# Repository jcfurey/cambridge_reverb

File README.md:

# Vox Cambridge Reverb (V1031/V1032) — Electronics Rebuild

Complete electronics rebuild of a Vox Cambridge Reverb solid-state guitar amplifier:
the original electronics are gutted and replaced with modern parts while preserving
the original functionality, the front/rear panel layout (no new holes), and the
chassis. Guitar-frequency and 10″ alnico-speaker optimized throughout.

> **Honesty up front:** the Part 1–10 design docs were **reconstructed** from a prior
> conversation (see `docs/PROVENANCE.md`); some values were gap-filled, and a few stages
> are designed substitutes. The KiCad project, BOM, order package and ngspice sims are
> **generated and tool-verified** — both boards are fully routed with 0 DRC errors, and
> `kicad/gen/verify.py` checks them pin for pin against the schematic and the
> datasheets. **Nothing has been built or measured.** A datasheet audit and new simulations
> found six faults in November 2026 that ERC and DRC could not see (errata #25–#30), and
> measuring the copper found a slotted ground plane and blind vias (errata #31);
> expect the bench to find more. Order one batch, bring it up on a series lamp.

## Core design decisions

| Block | Replacement |
|-------|-------------|
| Power amp | LM1875T (replaces germanium push-pull; eliminates driver transformer T2) |
| Preamp JFETs | MMBF5457 (SOT-23: direct on the SMD variant, on an adapter for THT) or J113 (2N5457 discontinued) — **availability watch**; pins 1 D / 2 S / 3 G (errata #18) |
| Reverb / tremolo | TL072 ×2 (no transformer T3): IC1 = tank driver + **active wet/dry summer**; IC2 = tremolo LFO + **output buffer** |
| Reverb pan | Accutronics 4FB2A1C (~1475 Ω input) — 8 Ω 4AB3C1B is **incompatible** |
| Tremolo modulation | Xvive VTL5C1 or DIY LED/LDR optocoupler (axial part, **pad 1 = LED cathode** — errata #25), driven by a TL072 Wien LFO — **symmetric, dual-gang 250 k speed pot, 0.6–10.6 Hz** (errata #19: the recovered single-arm pot could not oscillate at tremolo rates); LED-limited LFO + **2N3904 emitter-follower LED driver, 14 dB depth** (errata #22: as drawn the vactrol LED ran at 7 mA DC — a fixed −20 dB pad with 1.7 dB of wobble) |
| Footswitch | Three contacts to ground on the original DIN connector: reverb off, tremolo off, **MRB on** — the MRB tank returns to ground *through* the pedal, so with no pedal the amp is flat (errata #27: the lines used to end on pull-downs and the 577 Hz band-pass was permanently in circuit) |
| Preamp gain | Two JFET stages, source-bypass caps `C_s1` / `C_s2` **optional and off by default**: 21 dB, clean to ~0.3 V pk; fitted they give 33 / 45 dB and an overdriven second stage (errata #28) |
| Power | Centre-tapped secondary into the KBP410G as a **two-diode full-wave** (link `JP_BR` open; fit it only for a single 24 V winding — errata #26: CT and the bridge's "−" were both grounded, a short across each half-winding); LM317T-regulated +17 V rail with **`C_adj`** and an RC-decoupled **`+17V_PRE`** rail for the JFET stages (errata #21: the regulator's noise sat 23 dB above the JFET floor); split `VBIAS_R`/`VBIAS_T`/`VBIAS_3` mid-rails; `VREG_IN` RC pre-filter; **bypassed LM1875 bias divider** (errata #21: as drawn it fed rail ripple ×23 to the speaker — 0.4 Vrms of hum) |
| Tone | **Bass + Treble** (the panel's pots) on a passive James / Thomas-Vox network with a TL074 buffer + make-up (IC3), 470 pF chime cap as a bright cap, and a **MID CUT toggle** (−9.6 dB @ ~800 Hz, broad) in the line-reverse switch hole — errata #20 (the recovered 470 pF-only coupling passed no bass at all) |

## What's verified (all via real tools — `kicad/gen/build.sh smd`, `kicad/gen/verify.py smd`)
- **One gate:** `kicad/gen/verify.py` — **90 of 90 checks** on the SMD board, 79 of 79 on the THT board (`kicad/reports/verify-*.txt`). It reads the finished files, not the generator's data: ERC, DRC, schematic-to-board parity pin for pin, a pin-function audit against the datasheets, net-level electrical assertions (clamp-diode direction, rectifier topology, electrolytic polarity at the DC operating point, supply pins, pot directions, footswitch), silkscreen, JLCPCB's published limits, the star-ground topology and a solve of the return currents in the routed copper, ground loops (on the board, through the hardware, through the wiring), geometric and DC offsets, the ground-system ("RF") rules measured on the finished copper, order-package consistency, and the SPICE suite with a schematic-to-netlist value cross-check.
- **Schematic:** generated by `kicad/gen/gen_kicad.py` → 8 hierarchical sheets, **ERC 0 violations** (KiCad 8.0.9). SMD build: 162 components + 29 test points, 89 nets; the THT build has 182 parts (that board is full: a few parts are single where the SMD board uses JLCPCB-basic multiples, and three bleeders live off the board).
- **The JLCPCB board** (`kicad/smd/`, **170 × 105 mm**, 4 layers): **256 of 256 connections routed, 0 DRC errors, 0 warnings** with JLCPCB's limits as constraints. 105 small parts (0805 / 1206 / SMA / SOT-23) are placed by JLCPCB; 36 through-hole parts — power devices, electrolytics, socketed op-amps, the bench-trimmed resistors, the bright cap — are soldered by hand. Every part is labelled on the silkscreen and every wiring pad says what it is for.
- **Star ground** (errata #32, `kicad/gen/ground_audit.py` → `kicad/reports/ground-*.md`): the planes are signal ground only; transformer centre tap, reservoir, speaker return and the LM1875's ground pin are separate routed nets that meet the planes through one 0 Ω link at the speaker's return terminal. Solving the routed copper as a resistor network puts the ground-return buzz at the speaker at **13 µV** at idle (the single-net board: 4.4 mV, 31 dBA at 1 m) and no speaker current in the planes.
- **Ground loops and offsets** (errata #37–#43, `kicad/gen/loop_audit.py`, `offset_audit.py`, `tidy_tracks.py` → `kicad/reports/loops-*.md`, `offsets-*.md`): no closed loop in any routed net; no ground copper under the mounting hardware; the wiring mistakes that would bridge the star are simulated and listed as eight rules in Part 3; the reverb tank's shield loop — the largest in the amplifier — is opened by a 10 Ω return on the SMD board (7 µV (7 hot) at the speaker for a reference stray field, against 903 µV (902 hot)). Every track end lands on the centre of its pad or via. Three DC faults found by simulating the real bias levels with no signal: the output buffer followed the tremolo oscillator's bias rail (0.37 V pp of LFO at the speaker, now 8 mV), the footswitch thumped (2.5 V pp, now 5 mV), and the vactrol's blocking capacitor charged its node while the tremolo was off (8–19 V pp on re-engaging, now 0.04 V).
- **Power-amp stability** (errata #35, `spice/ac_pa_stability.cir`): the roll-off capacitor across the LM1875's feedback resistor is gone — it took the noise gain of a gain-≥-10 amplifier to 1 (−9° / −1° of phase margin in a three-pole model); the 7.7 kHz roll-off is an RC at the input, +68° / +76°.
- **Ground system** (errata #31, `kicad/gen/rf_audit.py` → `kicad/reports/rf-*.md`): signal / **solid ground** / signal / **solid ground**, nothing routed on a plane, each signal layer 0.21 mm from its own plane; plane openings sized by the holes so no slot forms along a row of pins (3 openings over 5 mm in the inner plane, was 31); copper 0.5 mm back from the edge with a ground via fence every 5 mm; a via beside every SMD ground pad and 340 ground vias in all, no point further than 15 mm from one; top pour 0.5 mm from every trace and 1.0 mm from high-impedance nets. Stray capacitance of every sensitive net is tabulated: the lowest corner is `TONE_OUT`, 25 pF → 101 kHz. All vias are plain through vias.
- **Order package** (`production/smd/`, built by `kicad/gen/fab_jlcpcb.py`): Gerber + drill zip, assembly BOM with **an LCSC part number on every one of its 28 lines** (each looked up in JLCPCB's library — stock, class, package; `kicad/gen/jlc_parts.py --check` re-reads them), pick-and-place file in JLCPCB's format with the SOT-23 rotation offset, assembly drawing. 21 basic / 4 preferred / **3 extended** part types: assembly fees ≈ $21 for five boards, ≈ $45 with the parts (`kicad/gen/jlc_cost.py`).
- **THT board** (`kicad/`, 190 × 115 mm, the original outline): same circuit, same stack, same star ground, all through-hole, **245 of 245 routed, 0 DRC errors, 0 warnings**; ground-return hum 27 µV. It is full — no room for the tank loop breaker or the three convenience bleeders, which Part 3 covers with wiring rules.
- **Routing:** `kicad/gen/route_board.py` autoroutes headlessly with Freerouting on the two signal layers; `kicad/gen/finish_routes.py`, a small maze router that applies the project's rules as written, closes the 7–13 links Freerouting leaves (signal-level branches of power nets, the tank drive), re-ordering and starting over if one finds no path; `kicad/gen/stitch.py` then stitches the grounds. Keepout areas between every part's pins, nets classed by impedance, RC stoppers at the two antenna inputs (errata #24). See `kicad/PCB-NOTES.md`.
- **BOM:** generated from the schematic by `kicad/gen/gen_bom.py` (1:1 with the netlist, no drift) → `bom/bom.csv` + `bom/bom-grouped.csv` (THT) and `bom/bom-smd*.csv` (variant).
- **Noise / hum / crosstalk / thermal** (`docs/06c-…`): `.noise` of the whole front end with the regulator's own noise (EIN 37 → 2.7 µV, SNR at 12 W 34 → 57 dB after errata #21), rail-ripple paths (hum 408 mV → 0.3 mV at the speaker), a vactrol-level tremolo model, a geometric **crosstalk audit** of both routed boards, and an electro-thermal LM1875 model (2.5 K/W sink: Tj 97 °C at 40 °C ambient, worst-case sine).
- **SPICE:** `spice/run_all.sh` runs 16 ngspice block checks (preamp bias, reverb driver, MRB engaged / bypassed, tremolo LFO and its **DC thumps and LFO feed-through with no signal**, power amp and its **loop stability**, **rail-aware** reverb summer and its **stability against stray capacitance**, **rail-aware** tone stack, Class-A stage, front-end noise, hum paths, tremolo depth with the footswitch, LM1875 thermal, **preamp headroom at pickup levels**) **plus 6 parameter sweeps** and saves every result table to **`spice/results/`** (committed evidence).

## Honest engineering notes (from the audit/roast passes — see `docs/roast-2026-06-16.md`)
- 🔴 **Output power ≈ 12 W, not 18 W.** A single 33.5 V rail can't swing the 17 V peak that 18 W into 8 Ω needs; the LM1875 ceilings at ~12 W clean (~1.8 dB down). Fine for a 10″ combo.
- 🔴 **Fit a MAINS (primary) fuse** — the design's other fuse is only on the secondary. Required for safety.
- 🔴 **Know your transformer before you wire it** (errata #26): centre tap to `CT` with `JP_BR` open, *or* a single winding with `JP_BR` fitted and `CT` empty.
- ⚠️ **Chassis fit:** the THT board is **190×115 mm** (the original 25-5274-2 outline), the JLCPCB board **170×105 mm**. Nobody has measured the actual chassis (errata #9); set `BW, BH` in `gen_pcb.py` and run `build.sh` if it disagrees — the placer and both routers adapt.

## Key constraints
- No new holes in original panels; all improvements internal only.
- MRB tuned to 600 Hz (original spec), switched by the footswitch; tremolo rate LED is PCB-mounted (diagnostic).
- Original 6-pin DIN footswitch connector and pedal retained (one contact to ground per effect).

## Repository layout

```
docs/         Parts 1–10, errata, PROVENANCE, audits (component-availability, roast)
kicad/        Generated KiCad project + gen/ scripts (build.sh, verify.py, …); symbols/
              footprints/ reports/; SCHEMATIC-BUILD / PCB-NOTES / PCB-AUDIT
spice/        ngspice block sims + run_all.sh + models/ (LTspice power-amp kept for provenance)
bom/          bom.csv (generated), bom-grouped.csv, cross-check
datasheets/   sourcing pointers (SOURCES.md)   photos/  capture checklist
production/   JLCPCB order package (smd/: Gerber zip, BOM with LCSC numbers, CPL) + checklist
```

## Tools
- **EDA / verification:** KiCad 8.0.9 (`kicad-cli`, `pcbnew` Python). `kicad/gen/build.sh smd|tht` rebuilds a board end to end (generate → Freerouting 1.9.0 → `finish_routes.py` → reports → order package → verify; needs Java, the Freerouting jar, xvfb, numpy, scipy, ngspice); `kicad/gen/verify.py smd|tht` checks an existing build
- **Datasheets:** `datasheets/` holds the manufacturer PDFs the footprints and pinouts were taken from, with a manifest (`SOURCES.md`: file, revision, checksum, which decision it backs)
- **Simulation:** ngspice (`spice/run_all.sh`); LTspice netlist kept for the power amp
- **PCB fab / sourcing:** JLCPCB · Mouser / Digikey

## Status
Reconstructed Parts 1–10 + errata, then verify / audit / roast passes and, in November
2026, a pinout and wiring audit that found what the rule checks could not (reversed
clamp diodes and vactrol LED, a shorted centre-tapped rectifier, a footswitch that
switched nothing, a preamp with no clean range — errata #25–#30), then a rebuild of the
copper to RF grounding practice (errata #31). Both boards are fully routed and
rule-clean, and the JLCPCB order package for the SMD / THT board is in `production/smd/`.
**Remaining, none of it doable from a keyboard:** measure the chassis, identify the
transformer, build one board and bring it up on a series lamp, trim the three JFET
source resistors, and tune tremolo depth and the MRB by ear. See `production/CHECKLIST.md`
and `CHANGELOG.md`.

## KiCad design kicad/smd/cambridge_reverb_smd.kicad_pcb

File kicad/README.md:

# kicad/

KiCad project files.

## Present now
- `cambridge_reverb.kicad_pro` — project with reconciled design rules and **three
  net classes** from the consistency pass: Default 0.5 mm / Power 1.5 mm /
  HighCurrent 2.5 mm (errata #11–13). `+33V5`/`SPK_P`/`SPK_N`/`PA_OUT` are pre-assigned
  to HighCurrent by net-name pattern.
- `symbols/cambridge_reverb.kicad_sym` — custom symbols: `VTL5C1`,
  `Reverb_Tank_4FB2A1C`, `Footswitch_DIN6`.
- `footprints/cambridge_reverb.pretty/` — `VTL5C1` (axial, from the PerkinElmer drawing: pad 1 = LED cathode, errata #25), `Inductor_MRB_1H_Toroid`
  (2-pad, 25 mm), **`TO-220-5_Vertical_P1.70mm_LM1875`** (TI NDH inline TO-220-5
  with 1.45 mm pads — fixes the annular-ring DRC error of the stock footprint,
  PCB-AUDIT §1), **`Bridge_KBP_P3.81mm`** (Diodes KBP410G, DS39310, pins
  + ~ ~ −), **`TestPoint_THT_D2.0mm_Label`** (bench test point, value printed on
  silk) and the **`WirePad_*`** wiring pads. `Wiring_Edge_Array_35` (35-pad edge connector) is also in the
  library but **currently unused** — `gen_pcb.py` places per-connector
  **`WirePad_1x0N_P2.54mm_D1.2mm` / `WirePad_1x0N_P5.08mm_D1.5mm`** pads (the Part 4
  signal / power wire-pad sizes) along the wiring edge instead; the 35-pad array
  is kept as a reference (roast R4).
- `sym-lib-table` / `fp-lib-table` — register the project libraries (`${KIPRJMOD}`).
- `netlist-notes.txt` — recovered per-sheet connections (power amp, reverb,
  tremolo, MRB).
- `SCHEMATIC-BUILD.md` — step-by-step to build the 8 hierarchical sheets.

## Generated schematic (now present)
- `cambridge_reverb.kicad_sch` (root) + 8 hierarchical sheets — `power_supply`,
  `preamp`, `tone_stack`, `reverb`, `tremolo`, `mrb`, `power_amp`, `switching`.
  They open in KiCad 7/8, **pass ERC with 0 violations** (KiCad 8.0.9), and
  netlist cleanly (154 components + 28 test points, 87 nets, 0 unconnected pins; the
  SMD build in `smd/` has 162 + 29 and 89 nets — errata #36, #38–#41).
- `symbols/cr_primitives.kicad_sym` — self-contained primitive symbols used by
  the generated sheets.
- `gen/gen_kicad.py` — the generator (regenerate: `python3 kicad/gen/gen_kicad.py`).
- `SCHEMATIC-BUILD.md` — how the sheets are wired, what's verified, and the
  known simplifications to finish before a build.

## PCB (generated: zoned placement + headless autoroute)
- `cambridge_reverb.kicad_pcb` — generated by `gen/gen_pcb.py`: 178 footprints
  placed into the **Part 5 floor-plan zones** (Input/Preamp | Tone | Reverb/Trem |
  Power Amp | PSU, left→right), off-board connectors on the bottom wiring edge,
  LM1875/LM317 on the top edge with the 10 mm keep-out, 4× M3 mounting holes,
  190×115 mm outline, **4 copper layers** (F.Cu signal + ground pour, In1 ground plane,
  In2 signal, B.Cu ground plane — nothing routed on a plane; ground via fence every
  5 mm), keepout areas between every part's pins, JLCPCB
  design rules + `cambridge_reverb.kicad_dru` impedance-class rules, every part labelled
  on the silkscreen. **Fully routed: 234 / 234 connections, 0 DRC errors, 0 warnings.**
- `gen/route_board.py` — **headless autoroute** via Freerouting (DSN → SES →
  import, GND pour refilled). Needs Java + the Freerouting jar (git-ignored; see
  the script docstring). It also injects the per-class *routing* clearances
  (HighCurrent 0.6 mm, TankDrive 1.2 mm) that `cambridge_reverb.kicad_dru` checks
  afterwards for tracks/vias. Routing status and numbers: `PCB-NOTES.md`.
- `gen/finish_routes.py` — a grid **maze router for the links Freerouting leaves open**
  (signal-level branches of power nets, the tank drive), applying the `.kicad_dru` rules
  as written; KiCad's DRC judges the result.
- `gen/build.sh smd|tht` — the whole chain in one command; `gen/verify.py smd|tht` —
  the gate (parity, pin-function audit, electrical assertions, order package, SPICE).
- `gen/fab_jlcpcb.py`, `gen/jlc_parts.py` — the **JLCPCB order package** in
  `production/smd/` and the looked-up LCSC part for every assembly line.
- `gen/stitch.py` — **ground vias**: a via beside every SMD ground pad before routing,
  a 7.5 mm stitching grid after it, unused inner-layer pad copper removed (errata #31).
  Also the via escapes for small parts on high-current nets (`fanout_taps`) and the
  charging pulses' own power-ground run (`split_ct` / `join_ct`, errata #43).
- `gen/tidy_tracks.py` — **geometric clean-up after routing**: every track end onto the
  centre of its pad or via, unused via escapes out, closed copper rings opened, plane
  necks under 0.2 mm closed; KiCad's DRC vetoes each change (errata #42).
- `gen/loop_audit.py` — **ground-loop audit** (`reports/loops-*.md`): closed loops in
  the routed copper, the area of the big current loops, copper under the mounting
  hardware, the power-ground star, wiring mistakes simulated, and the loops that close
  off the board priced for a reference stray field (errata #40, #41, #43).
- `gen/offset_audit.py` — **offsets audit** (`reports/offsets-*.md`): track ends,
  placement centroids and rotations, nets with no DC path, supply-trace voltage drops
  (errata #39, #42).
- `gen/ground_audit.py` — the **ground-return solver** behind both (`reports/ground-*.md`,
  errata #32).
- `gen/rf_audit.py` — **ground and parasitics audit** of the finished copper: plane
  openings, edge pull-back, pour gaps, fence and stitching density, and the stray
  capacitance of every sensitive net with the corner it makes (`reports/rf-*.md`).
- `gen/crosstalk_audit.py` — geometric **crosstalk screen** of a routed board:
  mutual capacitance of parallel runs between power/AC/tank-drive nets and the
  sensitive nodes, coupled level vs signal, loop gain (Part 6c §4).
- `gen/jlc_cost.py` — JLCPCB assembly **cost model** from the generated BOM (joints,
  basic vs extended part types) — Part 4.
- `gen/check.sh tht|smd [--no-regen]` — regenerate + ERC/DRC with the **JLCPCB
  fab limits** stored in both `.kicad_pro` files (hole-to-hole 0.5, hole-to-copper
  0.3, annular 0.18, mask dam 0.1 mm …) and the custom `.kicad_dru` rules.

## `smd/` — the mixed SMD/THT variant (same schematic, second footprint profile)
- `smd/cambridge_reverb_smd.kicad_pro/.kicad_sch` + the 8 sheets, `smd/cambridge_reverb_smd.kicad_pcb`
  (**170 × 105 mm**; fully routed, 0 DRC errors — the board `production/smd/` is built from): generated with `--profile smd` by the
  same scripts. Small passives and semis are SMD (0805 R, 1206 C,
  SMA D, SOT-23 JFETs / BJT); power parts, all electrolytics, the socketed
  TL072s / TL074, the bench-trimmed JFET source resistors, connectors and test points stay
  THT. Lib tables point at the shared `../symbols` / `../footprints`.
  Details and routing status: `PCB-NOTES.md` (SMD variant section).

## Still to do
- Confirm the board size against the measured chassis (errata #9), then order per
  `production/smd/README.md` and `production/CHECKLIST.md`.
- The copper is machine-routed and rule-clean, not hand-tuned: look it over in the GUI if
  you care how it looks. `gerbers/` is a scratch folder for manual exports; the order
  package lives in `production/smd/`.

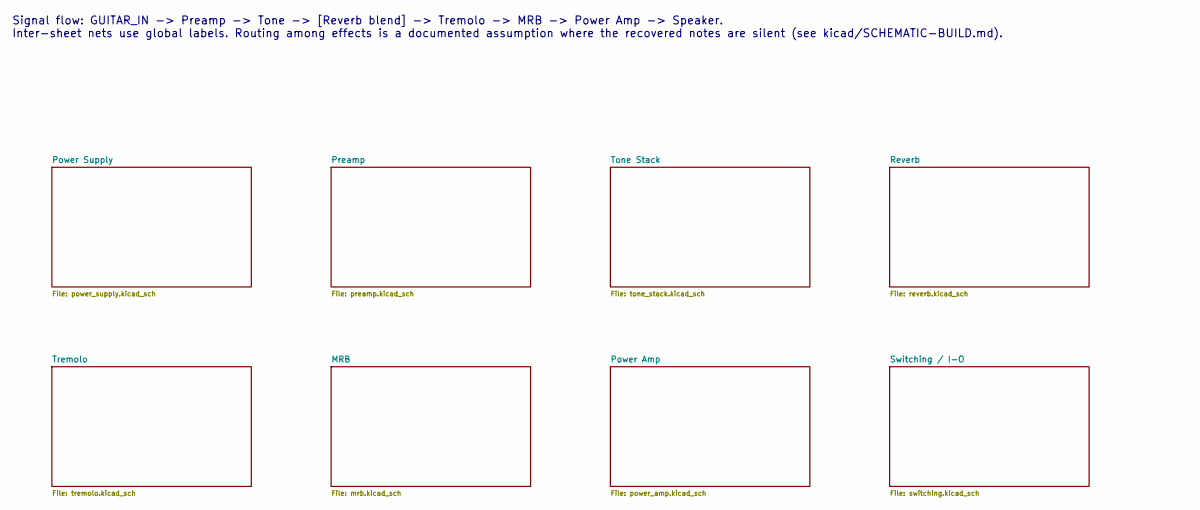
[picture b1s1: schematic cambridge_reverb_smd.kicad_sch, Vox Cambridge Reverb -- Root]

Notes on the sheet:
Signal flow: GUITAR_IN -> Preamp -> Tone -> [Reverb blend] -> Tremolo -> MRB -> Power Amp -> Speaker. Inter-sheet nets use global labels. Routing among effects is a documented assumption where the recovered notes are silent (see kicad/SCHEMATIC-BUILD.md).

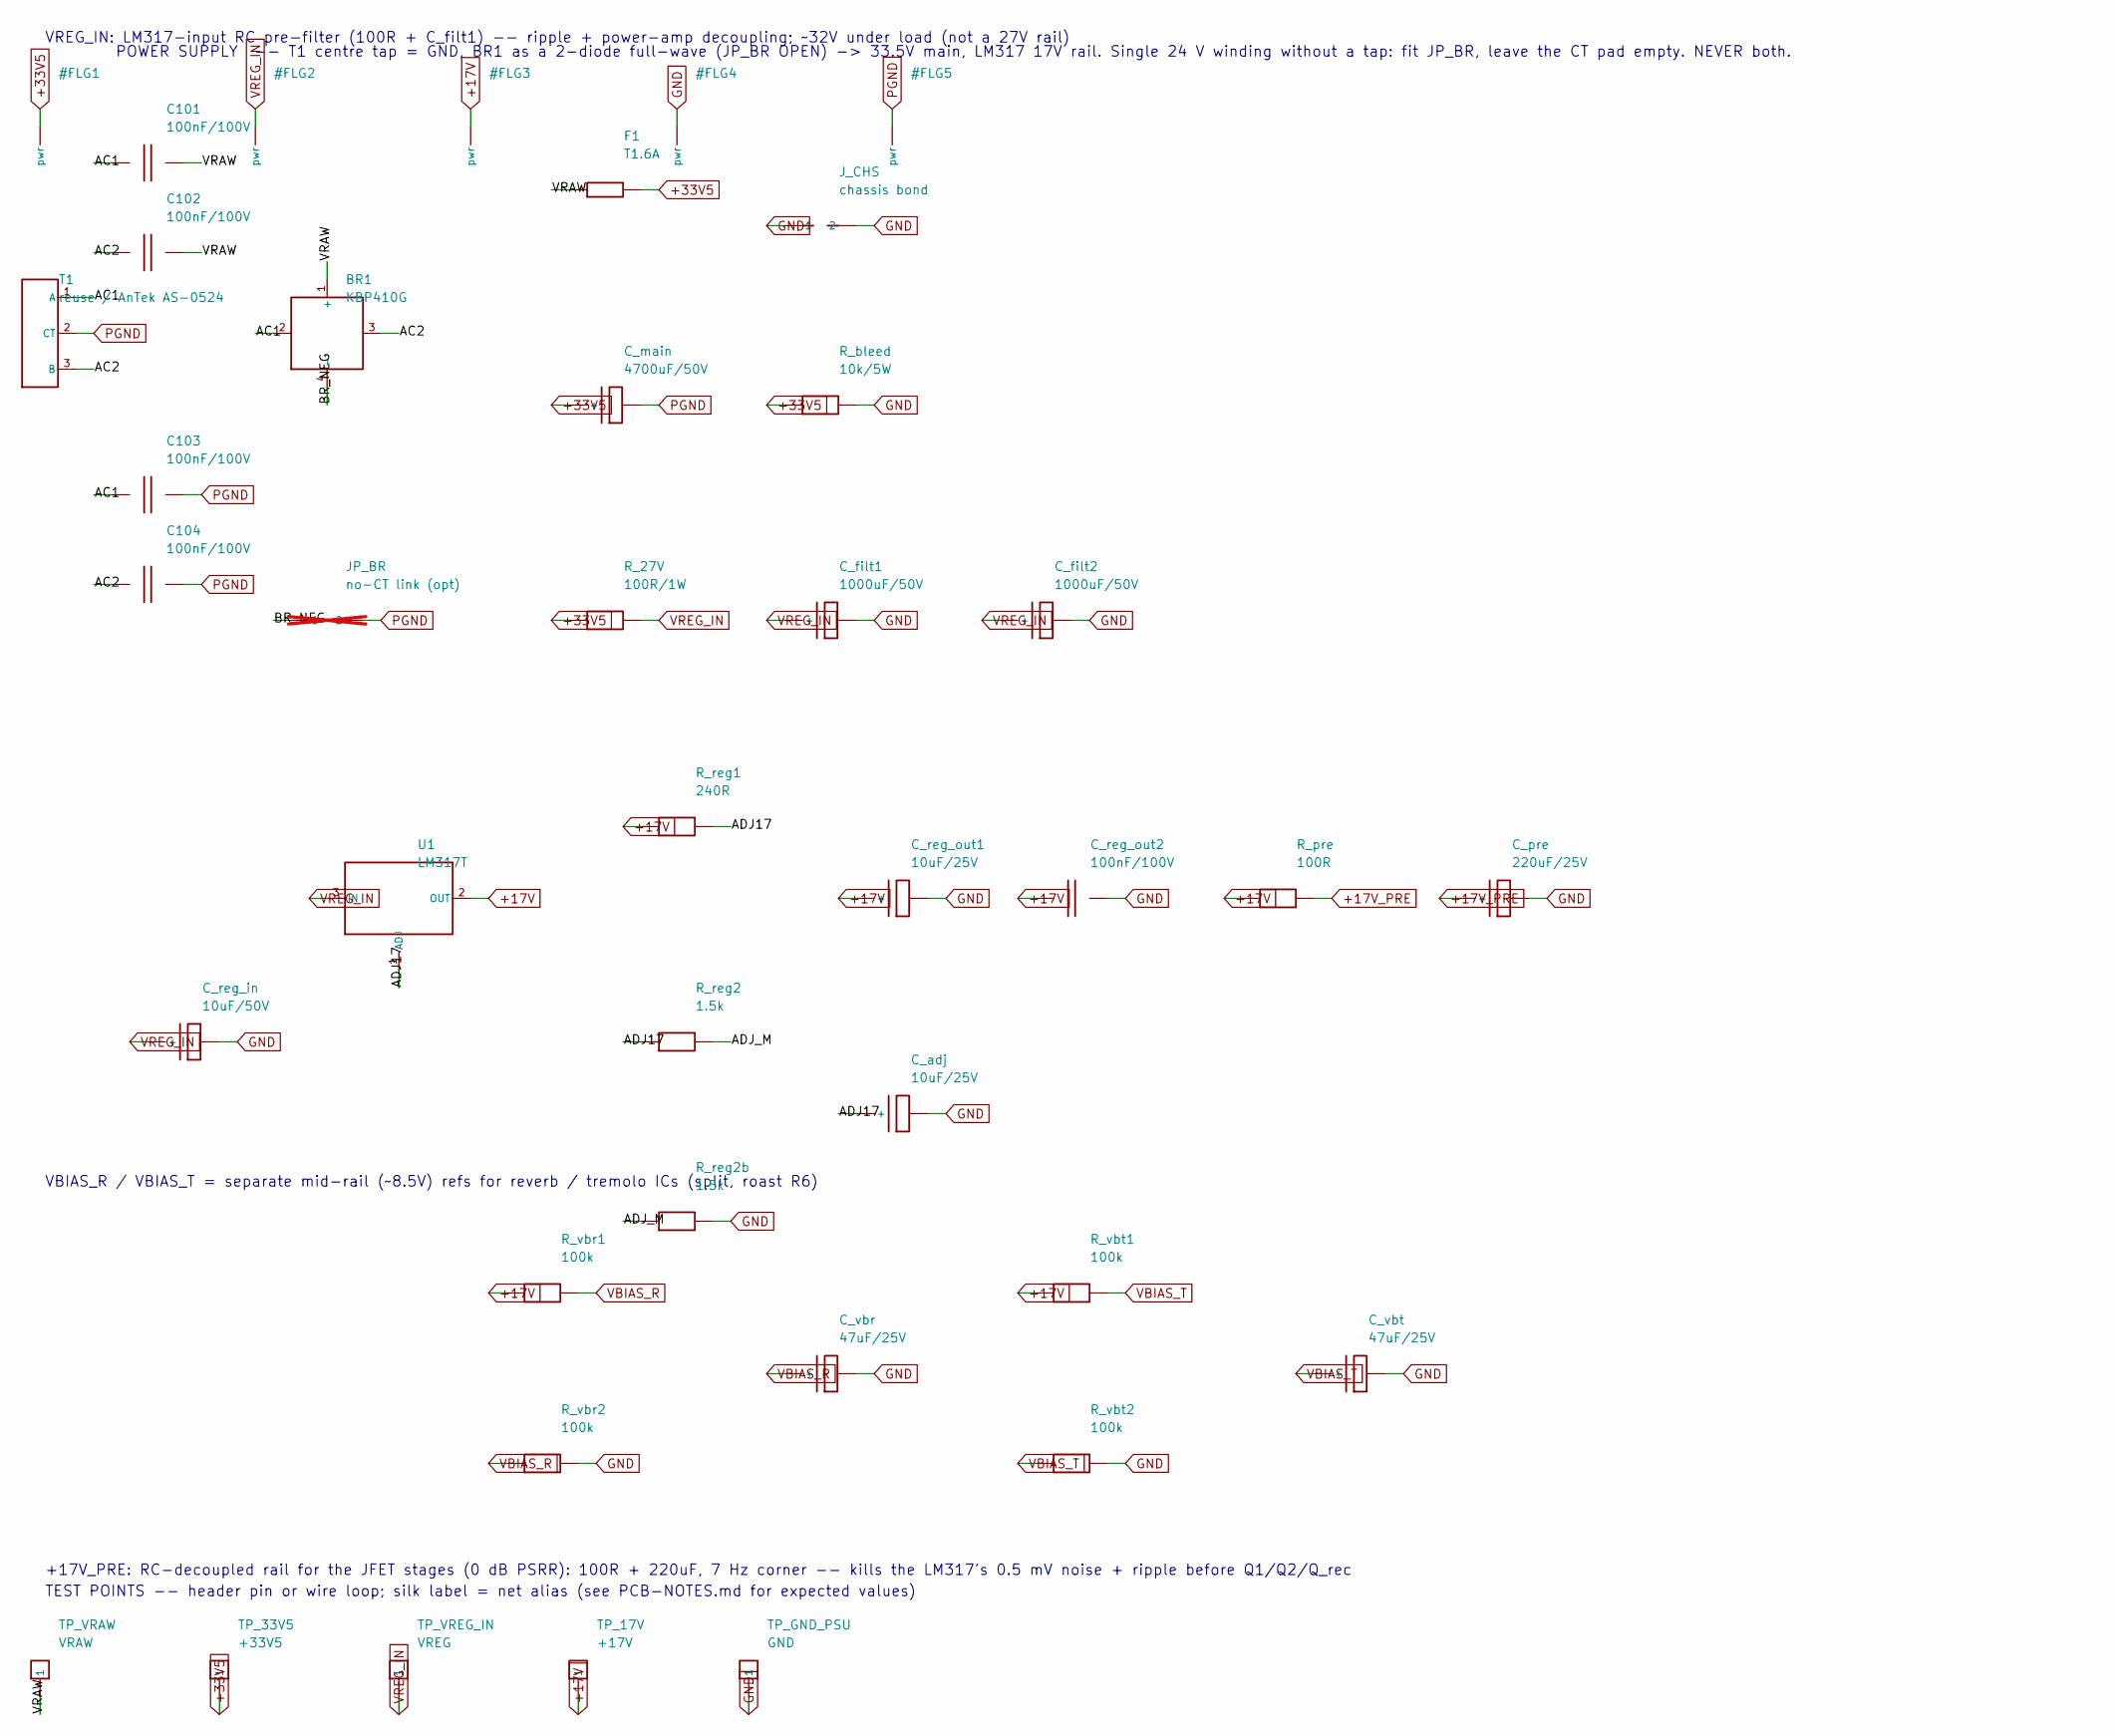
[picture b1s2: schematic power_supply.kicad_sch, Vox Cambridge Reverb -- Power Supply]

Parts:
BR1: KBP410G; Bridge_KBP_P3.81mm
C101, C102, C103, C104: 100nF/100V; C_0805_2012Metric
C_adj: 10uF/25V; CP_Radial_D5.0mm_P2.00mm
C_filt1, C_filt2: 1000uF/50V; CP_Radial_D12.5mm_P5.00mm
C_main: 4700uF/50V; CP_Radial_D18.0mm_P7.50mm
C_pre: 220uF/25V; CP_Radial_D6.3mm_P2.50mm
C_reg_in: 10uF/50V; CP_Radial_D5.0mm_P2.50mm
C_reg_out1: 10uF/25V; CP_Radial_D5.0mm_P2.50mm
C_reg_out2: 100nF/100V; C_0805_2012Metric
C_vbr: 47uF/25V; CP_Radial_D6.3mm_P2.50mm
C_vbt: 47uF/25V; CP_Radial_D6.3mm_P2.50mm
F1: T1.6A; Fuseholder_Clip-5x20mm_Eaton_1A5601-01_Inline_P20.80x6.76mm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
JP_BR: no-CT link (opt); WirePad_1x02_P5.08mm_D1.5mm; not fitted
J_CHS: chassis bond; WirePad_1x02_P5.08mm_D1.5mm
R_27V: 100R/1W; R_Axial_DIN0414_L11.9mm_D4.5mm_P15.24mm_Horizontal
R_bleed: 10k/5W; R_Axial_Power_L20.0mm_W6.4mm_P25.40mm
R_pre: 100R; R_0805_2012Metric
R_reg1: 240R; R_0805_2012Metric
R_reg2, R_reg2b: 1.5k; R_0805_2012Metric
R_vbr1, R_vbr2: 100k; R_0805_2012Metric
R_vbt1, R_vbt2: 100k; R_0805_2012Metric
T1: reuse / AnTek AS-0524; WirePad_1x03_P5.08mm_D1.5mm
TP_17V: +17V; TestPoint_THT_D2.0mm_Label
TP_33V5: +33V5; TestPoint_THT_D2.0mm_Label
TP_GND_PSU: GND; TestPoint_THT_D2.0mm_Label
TP_VRAW: VRAW; TestPoint_THT_D2.0mm_Label
TP_VREG_IN: VREG; TestPoint_THT_D2.0mm_Label
U1: LM317T; TO-220-3_Vertical

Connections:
+17V: C_reg_out1.1 (+), C_reg_out2.1, R_pre.1, R_reg1.1, R_vbr1.1, R_vbt1.1, TP_17V.1, U1.2 (OUT); also elsewhere on the board
+17V_PRE: C_pre.1 (+), R_pre.2; also elsewhere on the board
+33V5: C_main.1 (+), F1.2, R_27V.1, R_bleed.1, TP_33V5.1; also elsewhere on the board
AC1: BR1.2, C101.1, C103.1, T1.1 (A)
AC2: BR1.3, C102.1, C104.1, T1.3 (B)
ADJ17: C_adj.1 (+), R_reg1.2, R_reg2.1, U1.1 (ADJ)
ADJ_M: R_reg2.2, R_reg2b.1
BR_NEG: BR1.4 (-), JP_BR.1
GND: C_adj.2, C_filt1.2, C_filt2.2, C_pre.2, C_reg_in.2, C_reg_out1.2, C_reg_out2.2, C_vbr.2, C_vbt.2, J_CHS.1, J_CHS.2, R_bleed.2, R_reg2b.2, R_vbr2.2, R_vbt2.2, TP_GND_PSU.1; also elsewhere on the board
PGND: C103.2, C104.2, C_main.2, JP_BR.2, T1.2 (CT); also elsewhere on the board
VBIAS_R: C_vbr.1 (+), R_vbr1.2, R_vbr2.1; also elsewhere on the board
VBIAS_T: C_vbt.1 (+), R_vbt1.2, R_vbt2.1; also elsewhere on the board
VRAW: BR1.1 (+), C101.2, C102.2, F1.1, TP_VRAW.1
VREG_IN: C_filt1.1 (+), C_filt2.1 (+), C_reg_in.1 (+), R_27V.2, TP_VREG_IN.1, U1.3 (IN)

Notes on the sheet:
POWER SUPPLY -- T1 centre tap = GND, BR1 as a 2-diode full-wave (JP_BR OPEN) -> 33.5V main, LM317 17V rail. Single 24 V winding without a tap: fit JP_BR, leave the CT pad empty. NEVER both.
VREG_IN: LM317-input RC pre-filter (100R + C_filt1) -- ripple + power-amp decoupling; ~32V under load (not a 27V rail)
+17V_PRE: RC-decoupled rail for the JFET stages (0 dB PSRR): 100R + 220uF, 7 Hz corner -- kills the LM317's 0.5 mV noise + ripple before Q1/Q2/Q_rec
VBIAS_R / VBIAS_T = separate mid-rail (~8.5V) refs for reverb / tremolo ICs (split, roast R6)
TEST POINTS -- header pin or wire loop; silk label = net alias (see PCB-NOTES.md for expected values)

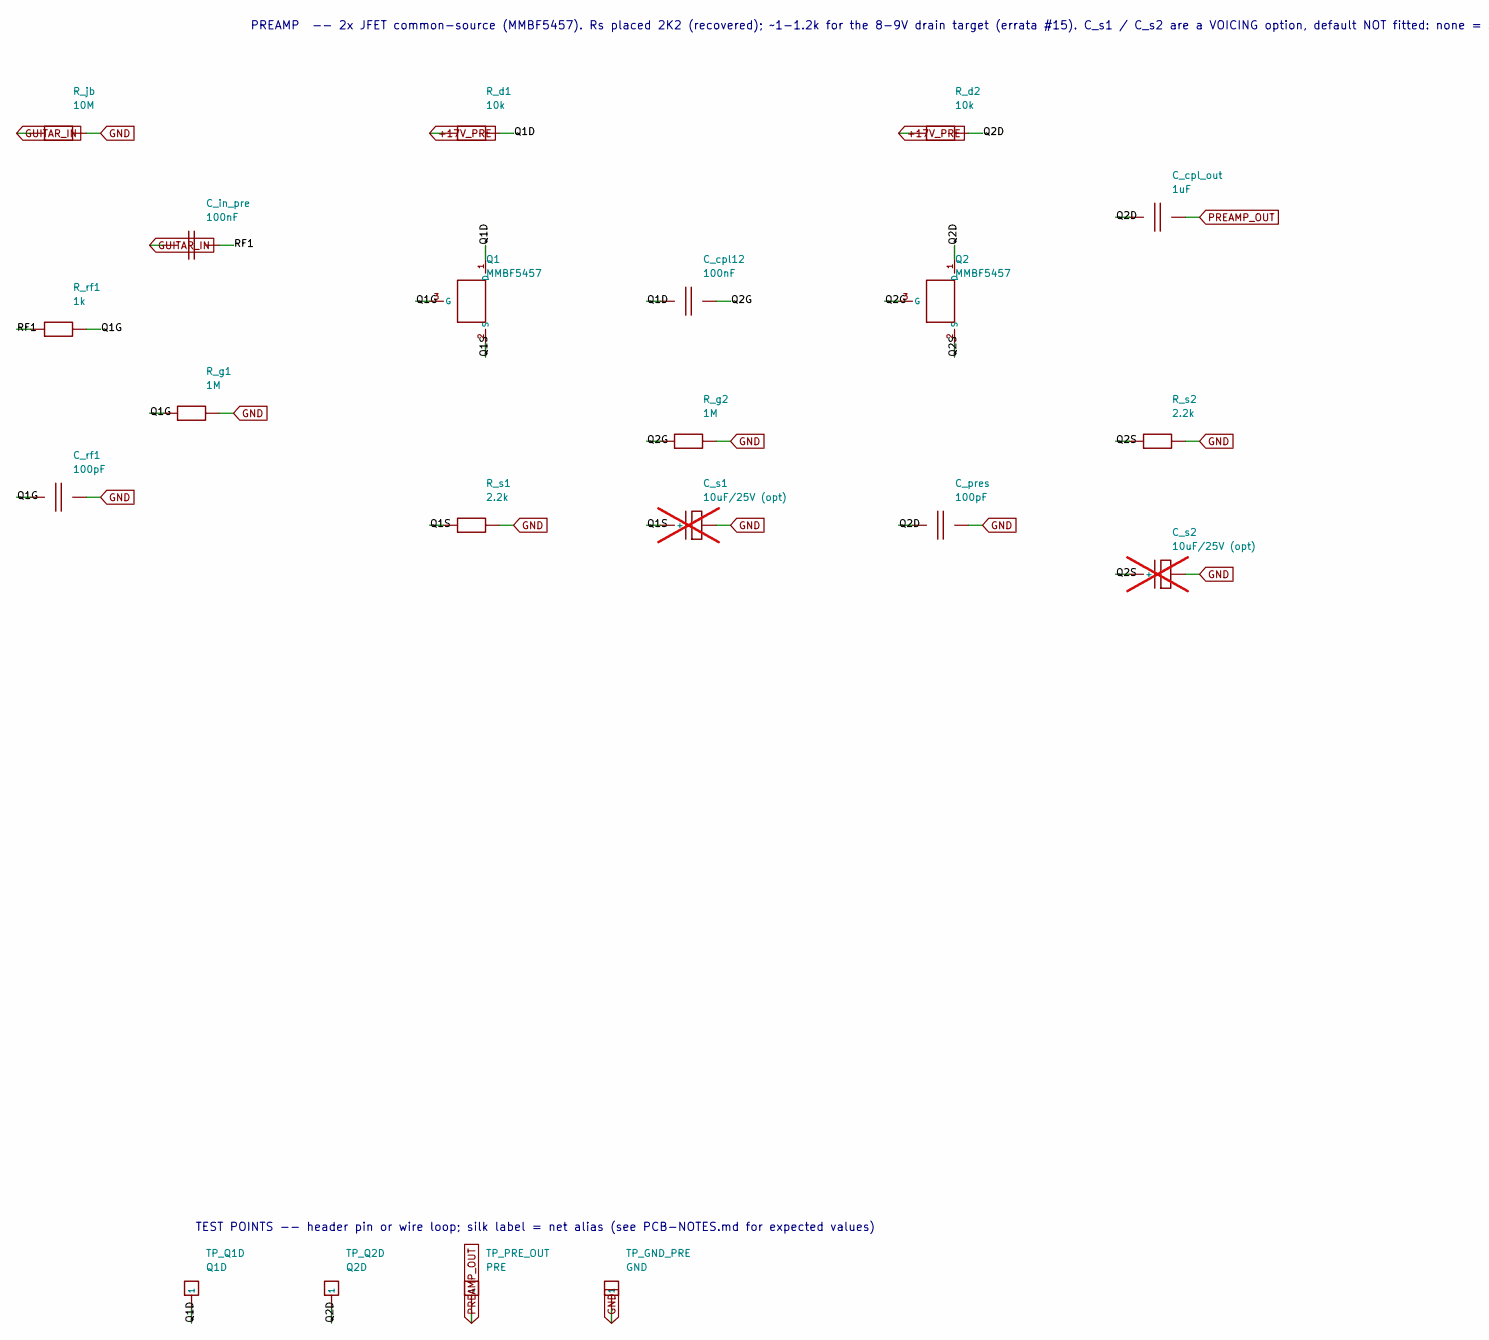
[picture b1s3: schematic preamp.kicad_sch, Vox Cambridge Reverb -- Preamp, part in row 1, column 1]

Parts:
C_cpl12: 100nF; C_1206_3216Metric
C_cpl_out: 1uF; C_1206_3216Metric
C_in_pre: 100nF; C_1206_3216Metric
C_pres: 100pF; C_0805_2012Metric
C_rf1: 100pF; C_0805_2012Metric
C_s1, C_s2: 10uF/25V (opt); CP_Radial_D5.0mm_P2.00mm; not fitted
Q1, Q2: MMBF5457; SOT-23
R_d1, R_d2: 10k; R_0805_2012Metric
R_g1, R_g2: 1M; R_0805_2012Metric
R_jb: 10M; R_0805_2012Metric
R_rf1: 1k; R_0805_2012Metric
R_s1, R_s2: 2.2k; R_Axial_DIN0207_L6.3mm_D2.5mm_P5.08mm_Vertical
TP_GND_PRE: GND; TestPoint_THT_D2.0mm_Label
TP_PRE_OUT: PRE; TestPoint_THT_D2.0mm_Label
TP_Q1D: Q1D; TestPoint_THT_D2.0mm_Label
TP_Q2D: Q2D; TestPoint_THT_D2.0mm_Label

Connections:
+17V_PRE: R_d1.1, R_d2.1; also elsewhere on the board
GND: C_pres.2, C_rf1.2, C_s1.2, C_s2.2, R_g1.2, R_g2.2, R_jb.2, R_s1.2, R_s2.2, TP_GND_PRE.1; also elsewhere on the board
GUITAR_IN: C_in_pre.1, R_jb.1; also elsewhere on the board
PREAMP_OUT: C_cpl_out.2, TP_PRE_OUT.1; also elsewhere on the board
Q1D: C_cpl12.1, Q1.1 (D), R_d1.2, TP_Q1D.1
Q1G: C_rf1.1, Q1.3 (G), R_g1.1, R_rf1.2
Q1S: C_s1.1 (+), Q1.2 (S), R_s1.1
Q2D: C_cpl_out.1, C_pres.1, Q2.1 (D), R_d2.2, TP_Q2D.1
Q2G: C_cpl12.2, Q2.3 (G), R_g2.1
Q2S: C_s2.1 (+), Q2.2 (S), R_s2.1
RF1: C_in_pre.2, R_rf1.1

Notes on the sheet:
PREAMP -- 2x JFET common-source (MMBF5457). Rs placed 2K2 (recovered); ~1-1.2k for the 8-9V drain target (errata #15). C_s1 / C_s2 are a VOICING option, default NOT fitted: none = 21 dB, clean to ~0.3 V pk; C_s1 only = 33 dB, breaks up above ~0.1 V; both = 45 dB, 8 % THD at 20 mV (spice/tran_preamp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
TEST POINTS -- header pin or wire loop; silk label = net alias (see PCB-NOTES.md for expected values)

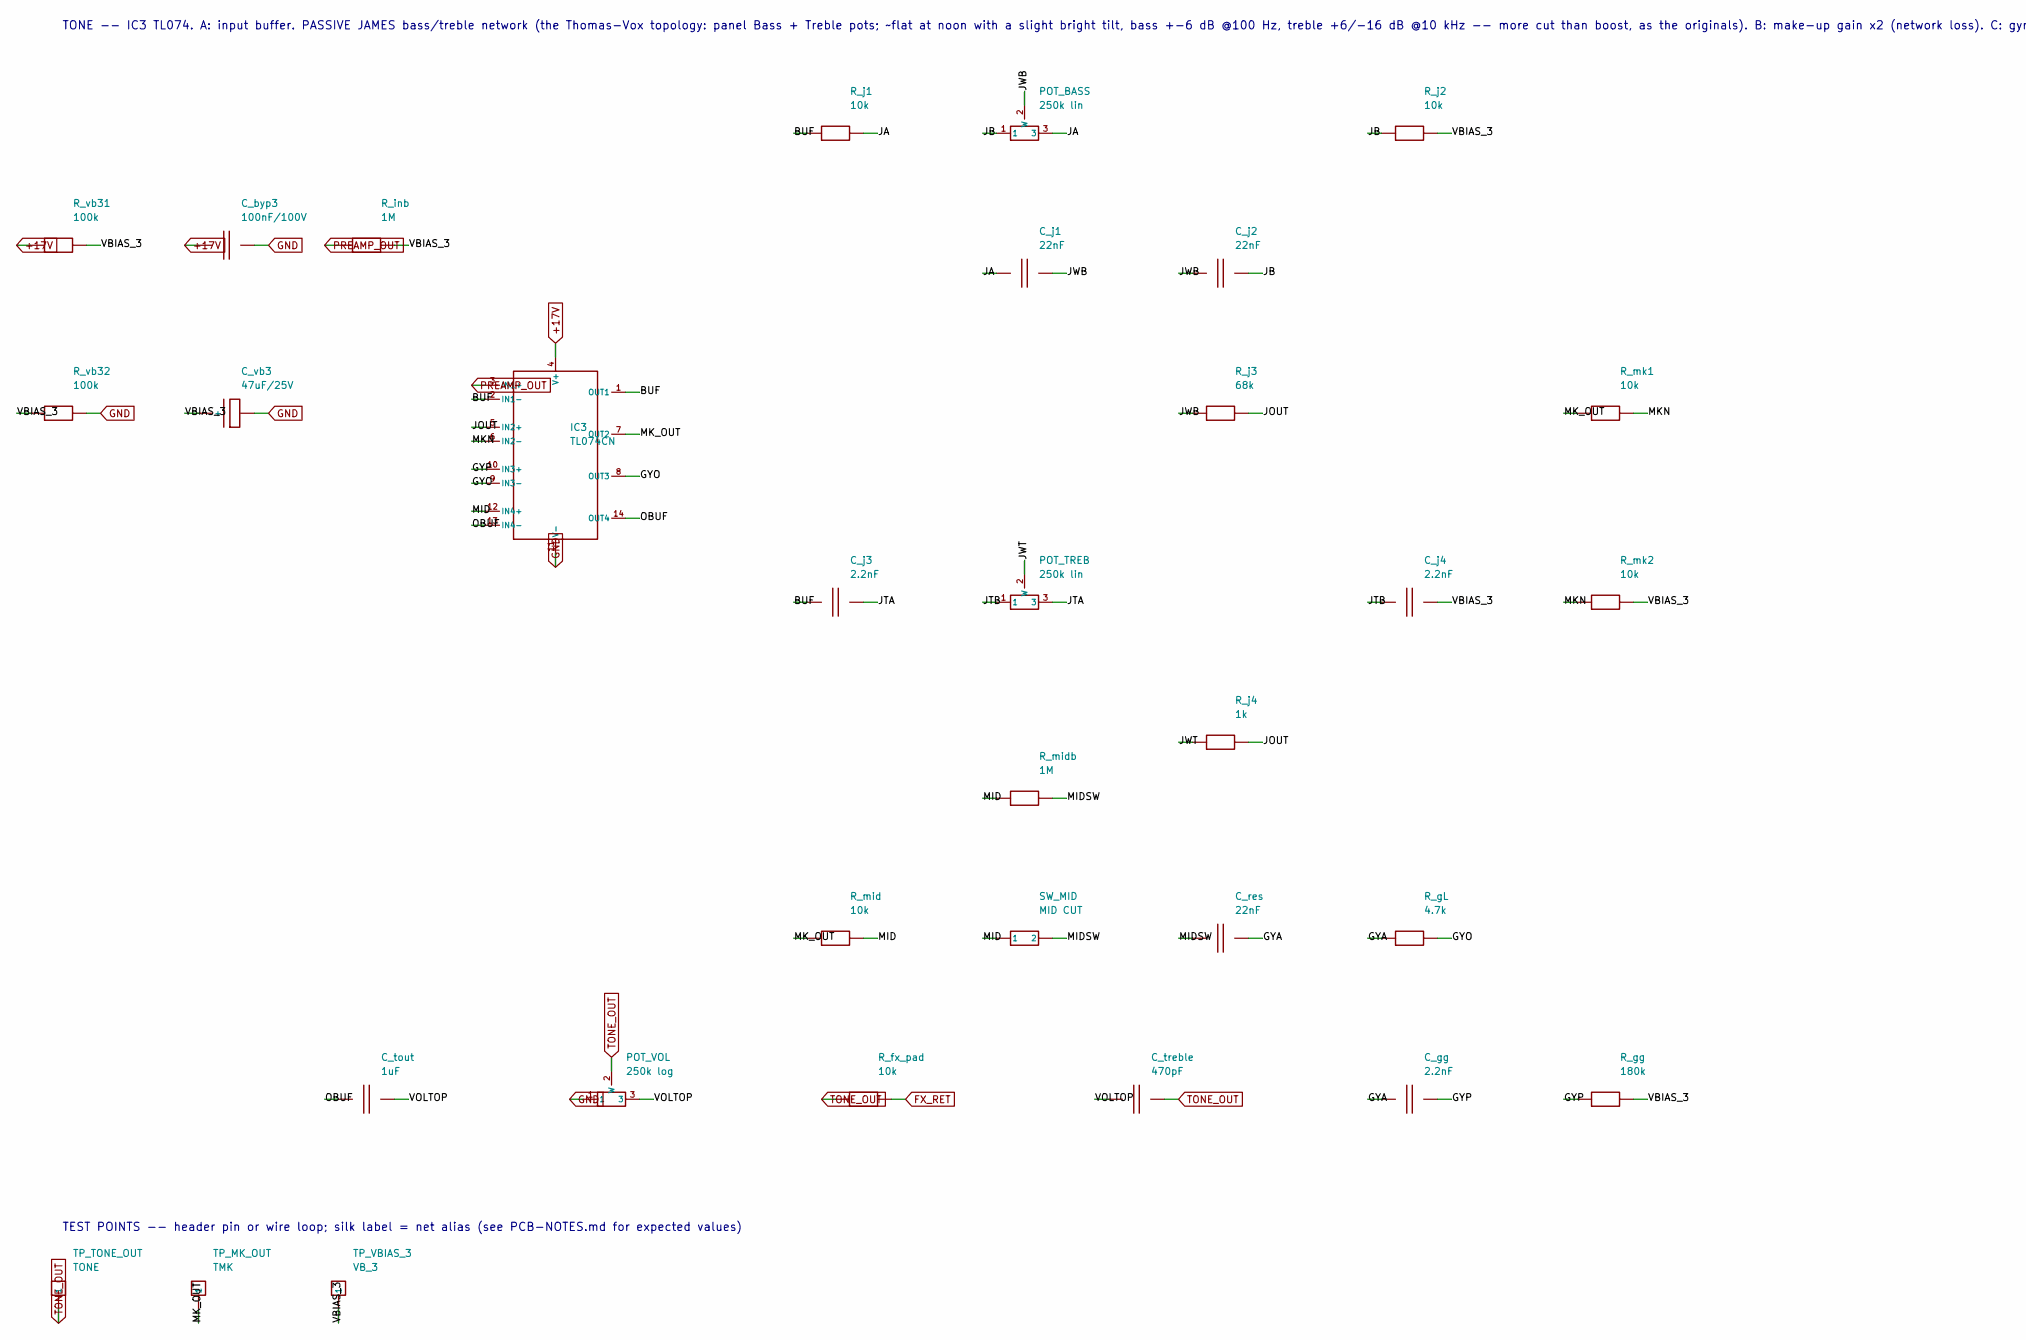
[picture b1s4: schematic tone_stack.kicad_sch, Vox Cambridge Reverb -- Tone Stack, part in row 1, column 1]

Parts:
C_byp3: 100nF/100V; C_0805_2012Metric
C_gg: 2.2nF; C_0805_2012Metric
C_j1, C_j2: 22nF; C_1206_3216Metric
C_j3, C_j4: 2.2nF; C_0805_2012Metric
C_res: 22nF; C_1206_3216Metric
C_tout: 1uF; C_1206_3216Metric
C_treble: 470pF; C_Disc_D7.5mm_W2.5mm_P5.00mm
C_vb3: 47uF/25V; CP_Radial_D6.3mm_P2.50mm
IC3: TL074CN; DIP-14_W7.62mm
POT_BASS: 250k lin; WirePad_1x03_P2.54mm_D1.2mm
POT_TREB: 250k lin; WirePad_1x03_P2.54mm_D1.2mm
POT_VOL: 250k log; WirePad_1x03_P2.54mm_D1.2mm
R_fx_pad: 10k; R_0805_2012Metric
R_gL: 4.7k; R_0805_2012Metric
R_gg: 180k; R_0805_2012Metric
R_inb: 1M; R_0805_2012Metric
R_j1, R_j2: 10k; R_0805_2012Metric
R_j3: 68k; R_0805_2012Metric
R_j4: 1k; R_0805_2012Metric
R_mid: 10k; R_0805_2012Metric
R_midb: 1M; R_0805_2012Metric
R_mk1, R_mk2: 10k; R_0805_2012Metric
R_vb31, R_vb32: 100k; R_0805_2012Metric
SW_MID: MID CUT; WirePad_1x02_P2.54mm_D1.2mm
TP_MK_OUT: TMK; TestPoint_THT_D2.0mm_Label
TP_TONE_OUT: TONE; TestPoint_THT_D2.0mm_Label
TP_VBIAS_3: VB_3; TestPoint_THT_D2.0mm_Label

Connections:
+17V: C_byp3.1, IC3.4 (V+), R_vb31.1; also elsewhere on the board
BUF: C_j3.1, IC3.1 (OUT1), IC3.2 (IN1-), R_j1.1
FX_RET: R_fx_pad.2; also elsewhere on the board
GND: C_byp3.2, C_vb3.2, IC3.11 (V-), POT_VOL.1, R_vb32.2; also elsewhere on the board
GYA: C_gg.1, C_res.2, R_gL.1
GYO: IC3.8 (OUT3), IC3.9 (IN3-), R_gL.2
GYP: C_gg.2, IC3.10 (IN3+), R_gg.1
JA: C_j1.1, POT_BASS.3, R_j1.2
JB: C_j2.2, POT_BASS.1, R_j2.1
JOUT: IC3.5 (IN2+), R_j3.2, R_j4.2
JTA: C_j3.2, POT_TREB.3
JTB: C_j4.1, POT_TREB.1
JWB: C_j1.2, C_j2.1, POT_BASS.2 (W), R_j3.1
JWT: POT_TREB.2 (W), R_j4.1
MID: IC3.12 (IN4+), R_mid.2, R_midb.1, SW_MID.1
MIDSW: C_res.1, R_midb.2, SW_MID.2
MKN: IC3.6 (IN2-), R_mk1.2, R_mk2.1
MK_OUT: IC3.7 (OUT2), R_mid.1, R_mk1.1, TP_MK_OUT.1
OBUF: C_tout.1, IC3.13 (IN4-), IC3.14 (OUT4)
PREAMP_OUT: IC3.3 (IN1+), R_inb.1; also elsewhere on the board
TONE_OUT: C_treble.2, POT_VOL.2 (W), R_fx_pad.1, TP_TONE_OUT.1; also elsewhere on the board
VBIAS_3: C_j4.2, C_vb3.1 (+), R_gg.2, R_inb.2, R_j2.2, R_mk2.2, R_vb31.2, R_vb32.1, TP_VBIAS_3.1
VOLTOP: C_tout.2, C_treble.1, POT_VOL.3

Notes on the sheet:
TONE -- IC3 TL074. A: input buffer. PASSIVE JAMES bass/treble network (the Thomas-Vox topology: panel Bass + Treble pots; ~flat at noon with a slight bright tilt, bass +-6 dB @100 Hz, treble +6/-16 dB @10 kHz -- more cut than boost, as the originals). B: make-up gain x2 (network loss). C: gyrator M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
TEST POINTS -- header pin or wire loop; silk label = net alias (see PCB-NOTES.md for expected values)

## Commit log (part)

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2026-06-14 Initial repo structure for Vox Cambridge Reverb rebuild
2026-06-14 Add reconstructed Parts 1-10, errata, BOM CSV, SPICE netlist, KiCad netlist notes
    Reconstructed from recovered conversation content; see docs/PROVENANCE.md.
    Recovered substantially verbatim: power-supply BOM, power-amp/tremolo/effects
    schematics, gain/bandwidth math, JLCPCB settings, troubleshooting tables,
    LM1875 SPICE netlist, errata issues 1-8, parts-to-reuse and verified-BOM tables.
2026-06-14 Consistency pass, BOM cross-check, KiCad project, and dir build-out
    Resolve errata Issues 9-17 with a fresh cross-document consistency pass;
    cross-check and complete the BOM; re-author the KiCad project and custom
    libraries; and fill the previously empty directories with reference content.
    Errata (docs/errata.md): board-dimension decision point (9); LM317 17V set
    resistor correction R_reg2 3.0k->3.09k for 17.0-17.5V (10); missing HighCurrent
    net class (11); via-drill/trace-width reconciliation (12,13); reverb-pan and
2026-06-14 Add validated ngspice block sims; validate KiCad files with kicad-cli
    Installed ngspice + kicad-cli and actually ran everything.
    KiCad: kicad-cli 7.0.11 parses/plots the custom symbol library and footprints
    cleanly (symbol lib re-saved in upgraded format); .kicad_pro is valid JSON.
    SPICE: added an ngspice-runnable companion set for five blocks (the LTspice
    power_amp_lm1875.cir is kept verbatim for provenance):
    - ac_power_amp_lm1875.cir -> gain 27.21 dB (23x); HF -3dB 6.83 kHz with the
2026-06-14 Generate wired hierarchical KiCad schematic (root + 8 sheets)
    Turn SCHEMATIC-BUILD.md from a build guide into actual generated, openable
    schematics. kicad/gen/gen_kicad.py emits a self-contained primitive symbol
    library (cr_primitives.kicad_sym) plus a root sheet and 8 hierarchical
    sub-sheets (power_supply, preamp, tone_stack, reverb, tremolo, mrb, power_amp,
    switching), wired with global labels (rails/cross-sheet) and local labels.
    Verified with kicad-cli 7.0.11: the hierarchy exports a netlist with
2026-06-14 Schematic passes KiCad 8 ERC (0 violations); add op-amp mid-rail bias
    Installed KiCad 8.0.9 and ran a real Electrical Rules Check on the generated
    hierarchy. Drove it to 0 violations:
    - snapped every pin/wire endpoint to the 1.27 mm connection grid (was 338
    endpoint_off_grid violations)
    - gave the footswitch lines FS_REV/FS_TREM/FS_MRB a real second endpoint via
    100k control pulldowns on the reverb/tremolo/mrb sheets (was 3 dangling labels)
2026-06-14 Generate auto-placed PCB (102 footprints, GND pour, board outline)
    Build cambridge_reverb.kicad_pcb from the schematic via kicad/gen/gen_pcb.py
    (KiCad 8 pcbnew API): assign a THT footprint to every component (standard libs
    for generics + the project footprints for VTL5C1 and the 1H toroid), place all
    102 footprints (off-board connectors on a bottom wiring-edge strip, toroid in a
    reserved spot), assign all 58 nets to pads, draw a 190x115 mm Edge.Cuts outline,
    and pour a bottom-layer GND plane. Footprint assignments also carry into the
2026-06-14 Route power-section demo (DRC-clean) + chassis-fit density check
    Power-section routing demonstration (kicad/power_section_demo.kicad_pcb): a small
    isolated board that routes the supply's +33V5 rail at 2.5 mm (HighCurrent class)
    and +17V at 1.5 mm (Power class), plus the LM317 ADJ node, over a GND pour.
    kicad-cli pcb drc -> 0 violations. Each rail is routed as a trunk in clear space
    with short stubs from the pads (crossing-free). +27V and VRAW are left as a
    ratsnest on purpose: +27V must cross the +17V trunk, i.e. on a single free layer
2026-06-14 Address Copilot review: fix SPK_P/SPK_N netclass pattern + doc/script nits
    Real fix:
    - kicad/cambridge_reverb.kicad_pro: HighCurrent netclass patterns matched
    SPKR+/SPKR-, but the actual nets are SPK_P/SPK_N -> the speaker current path
    would have fallen back to the Default class (undersized tracks/vias). Patterns
    now match the real net names. Updated the SPKR± references in kicad/README.md
    and production/CHECKLIST.md to match.
2026-06-14 first open lol
2026-06-14 Audit pass: center schematic pages, PCB layout audit, SPICE audit
    Schematic: gen_kicad.py now defers draw-op emission, computes each sheet's
    content bounding box, and translates it to the page center (grid-snapped so pins
    stay on the 1.27mm grid). All 8 sheets are centered on the page instead of
    crammed top-left; ERC still 0 violations.
    PCB: full category-by-category audit in kicad/PCB-AUDIT.md (footprints,
    placement, net classes, copper/GND, routing) with prioritized fixes. Applied:
2026-06-14 Component availability/sockets/current/noise audit; require IC sockets
    Add docs/component-availability-audit.md:
    - Availability tiers: jellybeans (TL072, LM317, diodes, bridge, passives);
    niche-but-stocked (LM1875 single-source, reverb tank, transformer, Fasel);
    WATCH list (small-signal JFETs going EOL industry-wide; VTL5C1 single-source
    Xvive). The two real single-points-of-failure are the JFETs and the LM1875 ->
    buy spares; alternatives noted for each.
2026-06-15 Keep LM317-input pre-filter (rename +27V->VREG_IN, 47R->100R) - corrected call
    On reflection my earlier "delete R_27V, feed LM317 from +33.5V" recommendation
    was wrong for a noise-conscious design: R_27V + C_filt1 is an RC pre-filter on
    the LM317 input AND decouples the preamp supply from the power amp's transient
    current draw on the +33.5V rail (the LM317's PSRR alone falls off with
    frequency). Deleting it would hurt noise.
    The real bug was the mislabeling: under the modern ~15 mA load the node sits at
2026-06-16 Roast pass (2026-06-16): fix missing mains fuse, correct 18W->~12W spec, +more
    Adversarial review (docs/roast-2026-06-16.md), every finding verified by math or
    file. Fixes applied:
    R1 (SAFETY, was missing): added a MAINS PRIMARY fuse. The only fuse was a 1A on
    the secondary DC rail, which doesn't protect against a primary/transformer/
    bridge fault. Added T800mA/250V (120V; ~T400mA at 230V) to BOM + Part 1 safety
    + Part 3.
2026-06-16 Redesign effects chain: active reverb summer + output buffer + split bias
    Resolves roast R3 (broken passive mixer) and R6 (shared VBIAS bleed), using the
    two spare TL072 halves and verifying with a rail-aware SPICE model.
    - Reverb wet/dry mix is now an ACTIVE inverting summer on IC1-B (dry always on,
    wet via POT_REV, unity each, low-Z out about VBIAS_R). Removed the broken
    passive R_dry_tap/R_blend1/R_blend2 (1M dry series made it ~all-wet into an
    unbuffered 110k node).
2026-06-16 Generate BOM from schematic (authoritative); complete missing schematic parts
    The BOM had drifted badly from the schematic (~20 parts in the schematic missing
    from the BOM, ~20 stale/renamed rows in the BOM). Root-caused two ways:
    1. Completed the SCHEMATIC -- added parts that were in Part 2 / the BOM but never
    actually placed: rectifier snubbers C101-C104, 2nd pre-filter C_filt2, and the
    tremolo SPEED/DEPTH pots (POT_SPD as a rheostat in the Wien series arm to vary
    frequency; POT_DPT scaling the LFO into the VTL1 LED for depth). 117 comps, ERC 0.
2026-06-16 Design + verify the tone stack (Vox treble-cut substitute)
    The tone sheet was a TBD placeholder (original 25-5274-2 values never recovered).
    Replaced with a working passive Vox-style control: Volume pot + a treble "cut"
    (C_cut 10nF + POT_TONE 100k to ground). Verified in spice/ac_tonestack.cir:
    flat at bright (-1.6 dB, just insertion loss), musical treble cut at the dark end
    (-9 dB @ 5 kHz, -14 dB @ 10 kHz). Clearly flagged as a designed substitute (the
    original panel may have had separate Treble/Bass) in the sheet note, cross-check
2026-06-16 Normalize BOM value strings; refresh stale top-level README
    - gen_kicad NV(): normalize value strings for a tidy/consolidated BOM (2K2->2.2k,
    4K7->4.7k, drop the " film" descriptor that the footprint already conveys).
    Cosmetic only; ERC 0, demo DRC 0, SPICE exit 0, BOM regenerated.
    - README rewritten to reflect the actual current state instead of the original
    reconstructed-docs snapshot: the generated + tool-verified KiCad/BOM/ngspice
    flow, the verified ~12 W power ceiling (not 18 W), the required mains fuse, the
2026-06-17 Explore Class-A power amp (sim + design note) -- AC15-style
    Adds spice/tran_classa_output.cir (transistor-level, single +33.5V rail) and
    docs/classA-power-amp.md. Sim shows the case for Class A and the cost:
    - class AB (small idle ~0.11A): THD ~1.05% (crossover notch)
    - Class A (idle ~0.49A, >= peak load current): THD ~0.0025% (no crossover)
    - the tax: ~16W continuous heat for ~1W of pure Class A (then slides to AB to
    the ~12W ceiling) -- "Class A for the first watt, AB beyond", ideal for guitar.
2026-06-17 Build Class-A power-amp variant (LM317 CCS-biased LM1875), alongside AB
    Per the scope choice (variant alongside AB, ~0.5A): kicad/gen/gen_classa.py emits
    a standalone, ERC-clean kicad/power_amp_classa.kicad_sch -- the same LM1875 stage
    plus U_ccs (LM317 as a constant-current sink, R_set 2.5R -> I=1.25/2.5=0.5A from
    PA_OUT to GND), so the LM1875 runs single-ended Class A up to ~1W into 8 ohm and
    reverts to push-pull AB above. The main board stays Class AB; this is a drop-in
    alternative.
